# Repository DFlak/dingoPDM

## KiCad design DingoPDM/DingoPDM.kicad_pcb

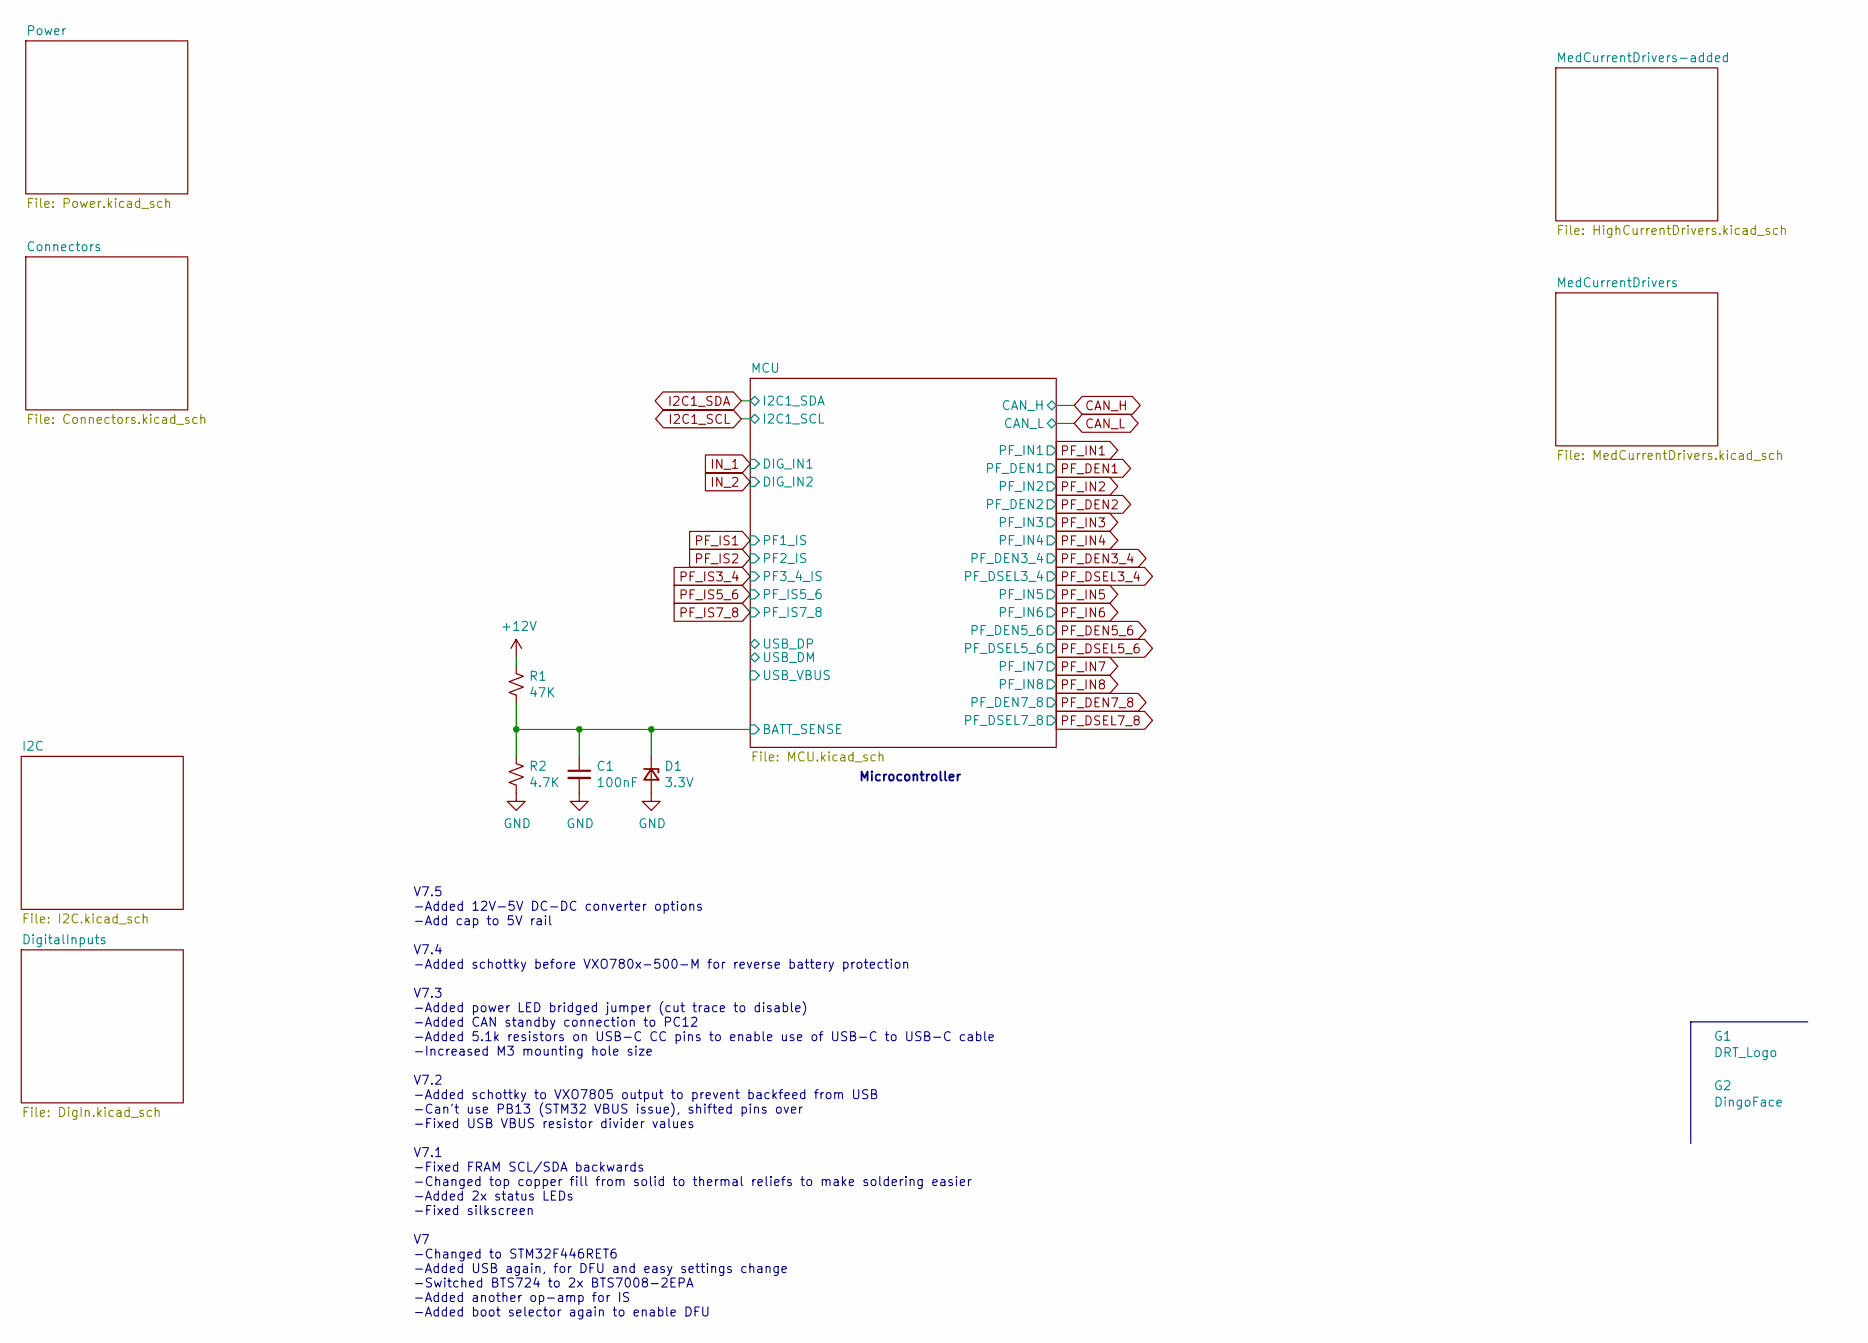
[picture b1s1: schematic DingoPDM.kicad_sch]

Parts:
C1: 100nF; C_0805_2012Metric; Digi-Key_PN 478-1395-1-ND
D1: 3.3V; D_SOD-323_HandSoldering; Digi-Key_PN 1727-5150-1-ND
G1: DRT_Logo; DRTLogo
G2: DingoFace; DingoFaceNoFill
R1: 47K; R_0805_2012Metric; Digi-Key_PN 311-47.0KCRCT-ND
R2: 4.7K; R_0805_2012Metric; Digi-Key_PN 311-4.70KCRCT-ND

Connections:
+12V: R1.1; also elsewhere on the board
/MCU/BATT_SENSE: C1.1, D1.1 (K), R1.2, R2.1; also elsewhere on the board
GND: C1.2, D1.2 (A), R2.2; also elsewhere on the board

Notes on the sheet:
Microcontroller
V7.5 -Added 12V-5V DC-DC converter options -Add cap to 5V rail V7.4 -Added schottky before VXO780x-500-M for reverse battery protection V7.3 -Added power LED bridged jumper (cut trace to disable) -Added CAN standby connection to PC12 -Added 5.1k resistors on USB-C CC pins to enable use of USB-C to 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

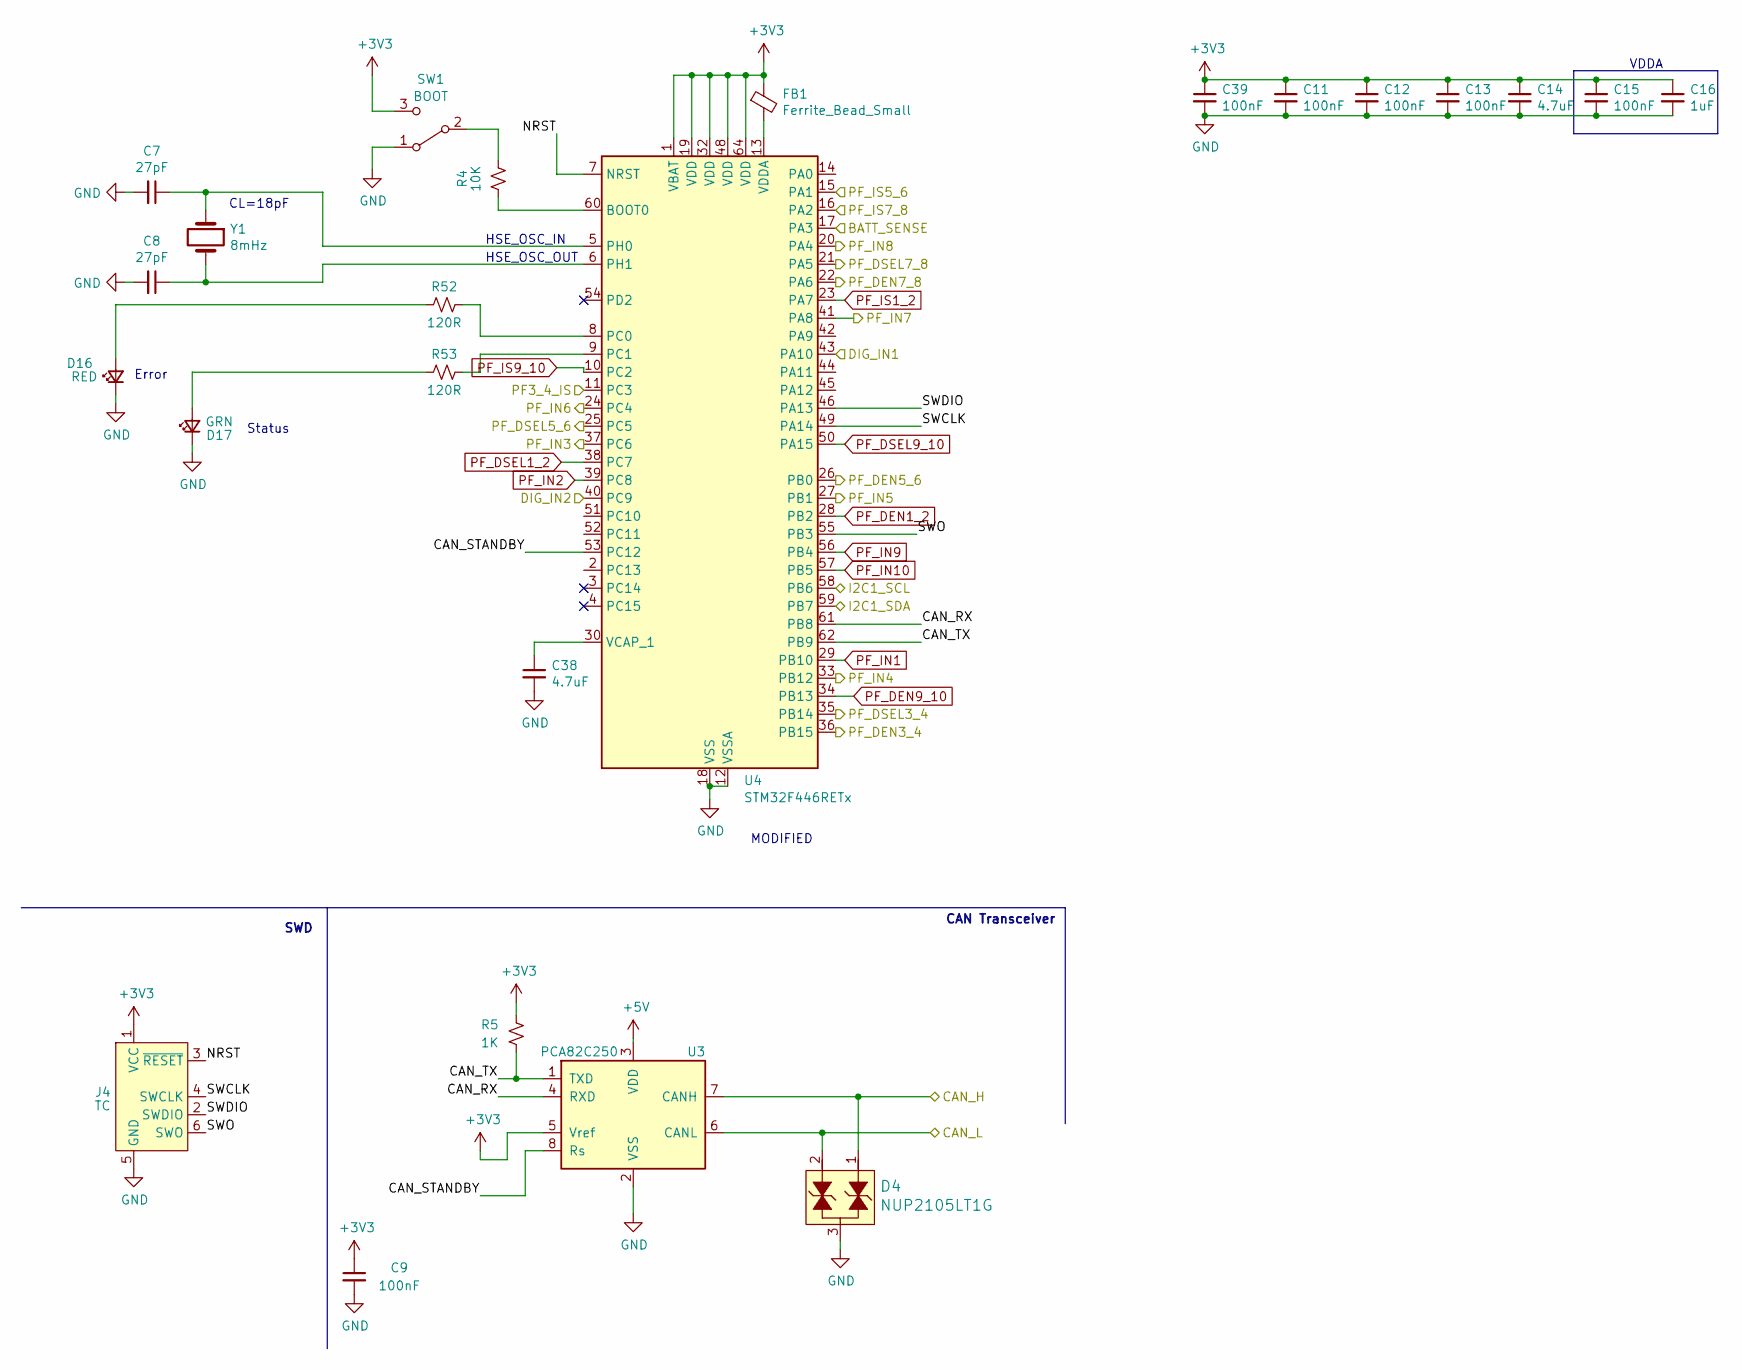
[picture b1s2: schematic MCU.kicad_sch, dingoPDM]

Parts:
C7, C8: 27pF; C_0805_2012Metric; Digi-Key_PN 478-10518-1-ND
C9, C11, C12, C13, C15, C39: 100nF; C_0805_2012Metric; Digi-Key_PN 478-1395-1-ND
C14, C38: 4.7uF; C_0805_2012Metric; Digi-Key_PN 1276-2873-1-ND
C16: 1uF; C_0805_2012Metric; Digi-Key_PN 311-1365-1-ND
D4: NUP2105LT1G; SOT-23-3; Digi-Key_PN NUP2105LT1GOSCT-ND
D16: RED; LED_0805_2012Metric; Digi-Key_PN 475-1278-1-ND
D17: GRN; LED_0805_2012Metric; Digi-Key_PN 475-1410-1-ND
FB1: Ferrite_Bead_Small; R_0805_2012Metric; Digi-Key_PN 490-1054-1-ND
J4: TC; Tag-Connect_TC2030-IDC-NL_2x03_P1.27mm_Vertical
R4: 10K; R_0805_2012Metric; Digi-Key_PN 311-10.0KCRDKR-ND
R5: 1K; R_0805_2012Metric; Digi-Key_PN 311-1.0KARCT-ND
R52, R53: 120R; R_0805_2012Metric; Digi-Key_PN 311-120CRCT-ND
SW1: BOOT; CJS-1200TB; Digi-Key_PN 563-CJS-1200TB1CT-ND
U3: PCA82C250; SOIC-8_3.9x4.9mm_P1.27mm; Digi-Key_PN 568-10316-1-ND
U4: STM32F446RETx; LQFP-64_10x10mm_P0.5mm; Digi-Key_PN 497-15376-ND
Y1: 8mHz; Crystal_SMD_5032-2Pin_5.0x3.2mm_HandSoldering; Digi-Key_PN 535-10630-1-ND

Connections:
+3V3: C9.1, C11.1, C12.1, C13.1, C14.1, C15.1, C16.1, C39.1, FB1.1, J4.1 (VCC), R5.2, SW1.3 (C), U3.5 (Vref), U4.1 (VBAT), U4.19 (VDD), U4.32 (VDD), U4.48 (VDD), U4.64 (VDD); also elsewhere on the board
+5V: U3.3 (VDD); also elsewhere on the board
/MCU/BATT_SENSE: U4.17 (PA3); also elsewhere on the board
/MCU/CAN_RX: U3.4 (RXD), U4.61 (PB8)
/MCU/CAN_STANDBY: U3.8 (Rs), U4.53 (PC12)
/MCU/CAN_TX: R5.1, U3.1 (TXD), U4.62 (PB9)
/MCU/NRST: J4.3 (~RESET), U4.7 (NRST)
/MCU/SWCLK: J4.4 (SWCLK), U4.49 (PA14)
/MCU/SWDIO: J4.2 (SWDIO), U4.46 (PA13)
/MCU/SWO: J4.6 (SWO), U4.55 (PB3)
CAN_H: D4.1, U3.7 (CANH); also elsewhere on the board
CAN_L: D4.2, U3.6 (CANL); also elsewhere on the board
GND: C7.2, C8.2, C9.2, C11.2, C12.2, C13.2, C14.2, C15.2, C16.2, C38.2, C39.2, D4.3, D16.1 (K), D17.1 (K), J4.5 (GND), SW1.1 (A), U3.2 (VSS), U4.12 (VSSA), U4.18 (VSS), U4.31 (VSS), U4.47 (VSS), U4.63 (VSS); also elsewhere on the board
I2C1_SCL: U4.58 (PB6); also elsewhere on the board
I2C1_SDA: U4.59 (PB7); also elsewhere on the board
IN_1: U4.43 (PA10); also elsewhere on the board
IN_2: U4.40 (PC9); also elsewhere on the board
unnamed: D16.2 (A), R52.2
unnamed: D17.2 (A), R53.2
unnamed: R4.1, SW1.2 (B)
unnamed: R4.2, U4.60 (BOOT0)
unnamed: R52.1, U4.8 (PC0)
unnamed: R53.1, U4.9 (PC1)
unnamed: C7.1, U4.5 (PH0), Y1.1
unnamed: C8.1, U4.6 (PH1), Y1.2
unnamed: C38.1, U4.30 (VCAP_1)
unnamed: FB1.2, U4.13 (VDDA)
PF_DEN1_2: U4.28 (PB2); also elsewhere on the board
PF_DEN3_4: U4.36 (PB15); also elsewhere on the board
PF_DEN5_6: U4.26 (PB0); also elsewhere on the board
PF_DEN7_8: U4.22 (PA6); also elsewhere on the board
PF_DEN9_10: U4.34 (PB13); also elsewhere on the board
PF_DSEL1_2: U4.38 (PC7); also elsewhere on the board
PF_DSEL3_4: U4.35 (PB14); also elsewhere on the board
PF_DSEL5_6: U4.25 (PC5); also elsewhere on the board
PF_DSEL7_8: U4.21 (PA5); also elsewhere on the board
PF_DSEL9_10: U4.50 (PA15); also elsewhere on the board
PF_IN1: U4.29 (PB10); also elsewhere on the board
PF_IN2: U4.39 (PC8); also elsewhere on the board
PF_IN3: U4.37 (PC6); also elsewhere on the board
PF_IN4: U4.33 (PB12); also elsewhere on the board
PF_IN5: U4.27 (PB1); also elsewhere on the board
PF_IN6: U4.24 (PC4); also elsewhere on the board
PF_IN7: U4.41 (PA8); also elsewhere on the board
PF_IN8: U4.20 (PA4); also elsewhere on the board
PF_IN9: U4.56 (PB4); also elsewhere on the board
PF_IN10: U4.57 (PB5); also elsewhere on the board
PF_IS1_2: U4.23 (PA7); also elsewhere on the board
PF_IS3_4: U4.11 (PC3); also elsewhere on the board
PF_IS5_6: U4.15 (PA1); also elsewhere on the board
PF_IS7_8: U4.16 (PA2); also elsewhere on the board
PF_IS9_10: U4.10 (PC2); also elsewhere on the board

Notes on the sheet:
SWD
Error
CAN Transceiver
HSE_OSC_IN
MODIFIED
CL=18pF
HSE_OSC_OUT
VDDA
Status

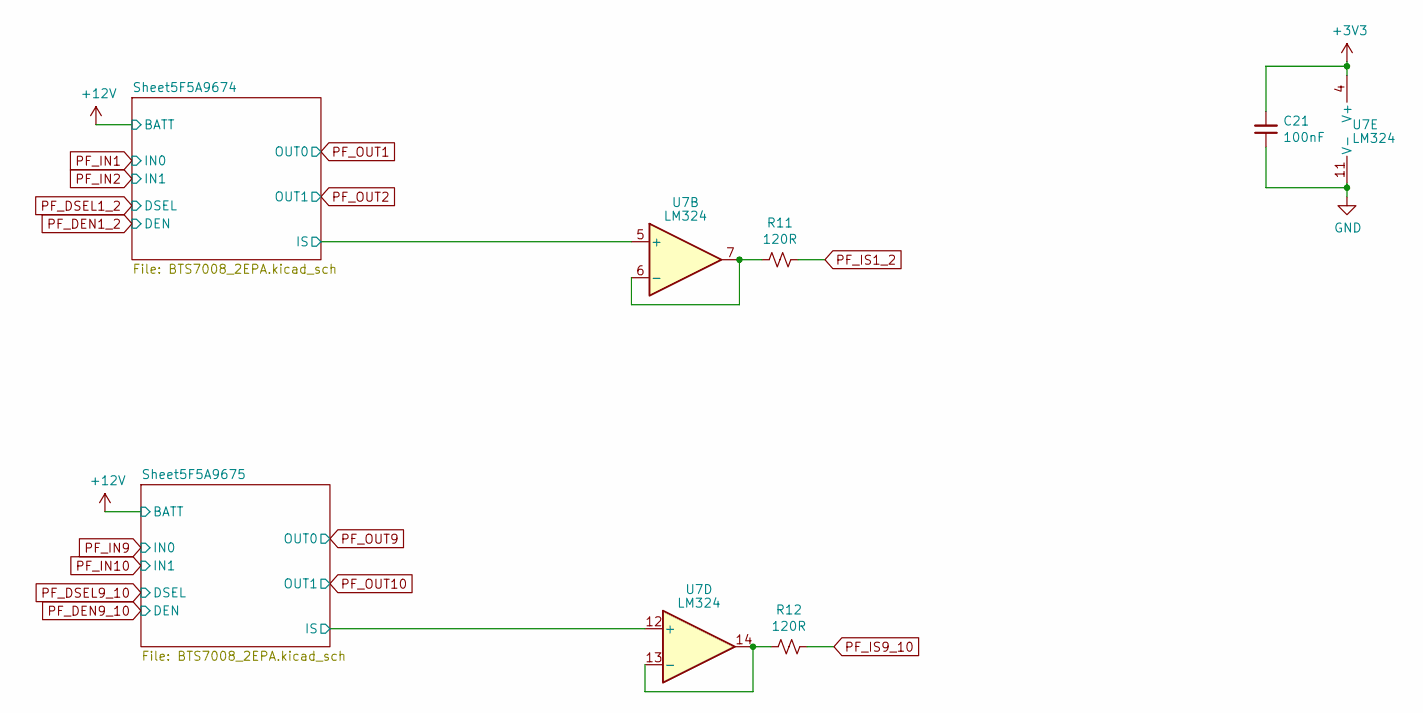
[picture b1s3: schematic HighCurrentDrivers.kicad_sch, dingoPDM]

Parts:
C21: 100nF; C_0805_2012Metric; Digi-Key_PN 478-1395-1-ND
R11, R12: 120R; R_0805_2012Metric; Digi-Key_PN 311-120CRCT-ND
U7: LM324; TSSOP-14_4.4x5mm_P0.65mm; Digi-Key_PN 497-7330-1-ND

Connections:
+3V3: C21.2, U7.4 (V+); also elsewhere on the board
/MedCurrentDrivers-added/Sheet5F5A9674/IS: U7.5 (+); also elsewhere on the board
/MedCurrentDrivers-added/Sheet5F5A9675/IS: U7.12 (+); also elsewhere on the board
/MedCurrentDrivers/Sheet5F5A9674/IS: U7.10 (+); also elsewhere on the board
GND: C21.1, U7.11 (V-); also elsewhere on the board
unnamed: R11.2, U7.6 (-), U7.7
unnamed 47: U7.8, U7.9 (-); also elsewhere on the board
unnamed: R12.2, U7.13 (-), U7.14
PF_IS1_2: R11.1; also elsewhere on the board
PF_IS9_10: R12.1; also elsewhere on the board

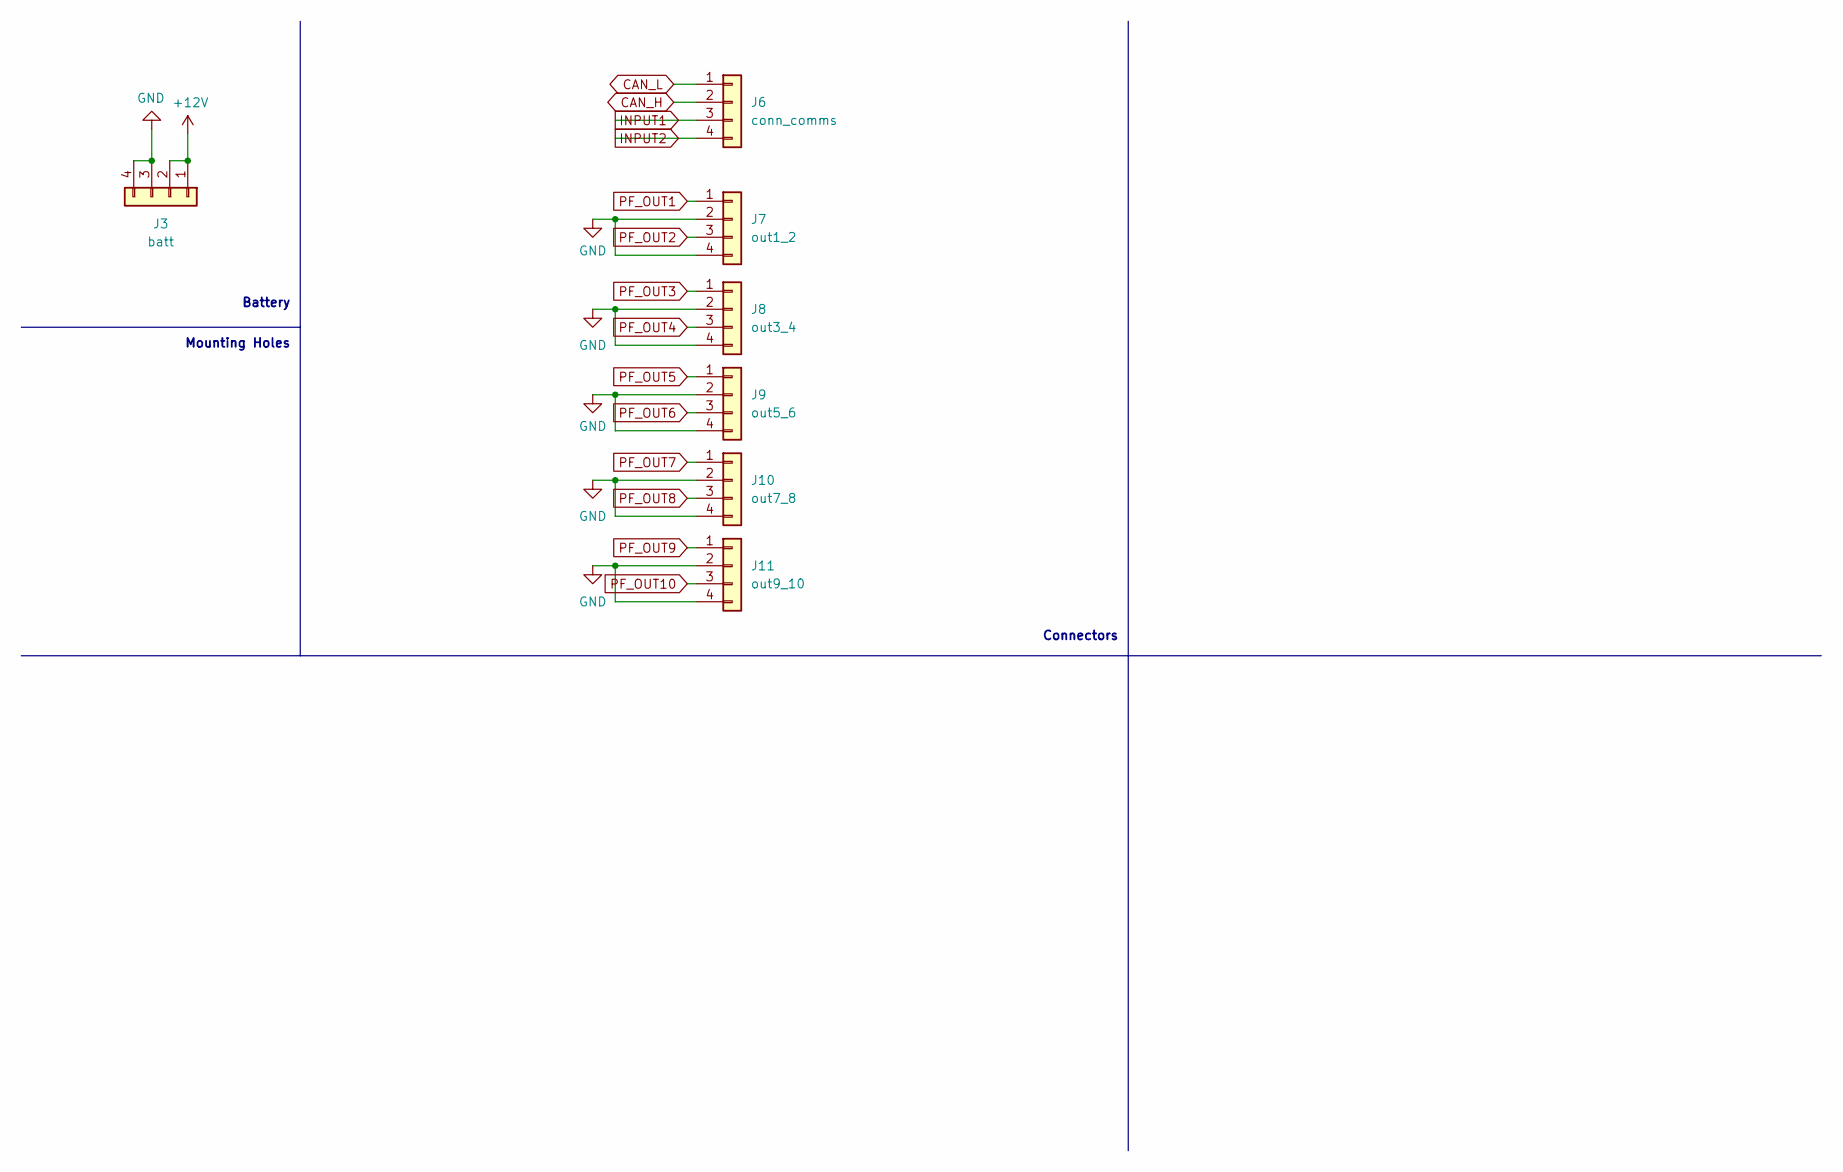
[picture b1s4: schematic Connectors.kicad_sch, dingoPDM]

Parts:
J3: batt; DIP-8_300_ELL
J6: conn_comms; DIP-8_300_ELL
J7: out1_2; DIP-8_300_ELL
J8: out3_4; DIP-8_300_ELL
J9: out5_6; DIP-8_300_ELL
J10: out7_8; DIP-8_300_ELL
J11: out9_10; DIP-8_300_ELL

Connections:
+12V: J3.1, J3.2; also elsewhere on the board
CAN_H: J6.2; also elsewhere on the board
CAN_L: J6.1; also elsewhere on the board
GND: J3.3, J3.4, J7.2, J7.4, J8.2, J8.4, J9.2, J9.4, J10.2, J10.4, J11.2, J11.4; also elsewhere on the board
INPUT1: J6.3; also elsewhere on the board
INPUT2: J6.4; also elsewhere on the board
PF_OUT1: J7.1; also elsewhere on the board
PF_OUT2: J7.3; also elsewhere on the board
PF_OUT3: J8.1; also elsewhere on the board
PF_OUT4: J8.3; also elsewhere on the board
PF_OUT5: J9.1; also elsewhere on the board
PF_OUT6: J9.3; also elsewhere on the board
PF_OUT7: J10.1; also elsewhere on the board
PF_OUT8: J10.3; also elsewhere on the board
PF_OUT9: J11.1; also elsewhere on the board
PF_OUT10: J11.3; also elsewhere on the board

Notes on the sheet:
Connectors
Battery
Mounting Holes

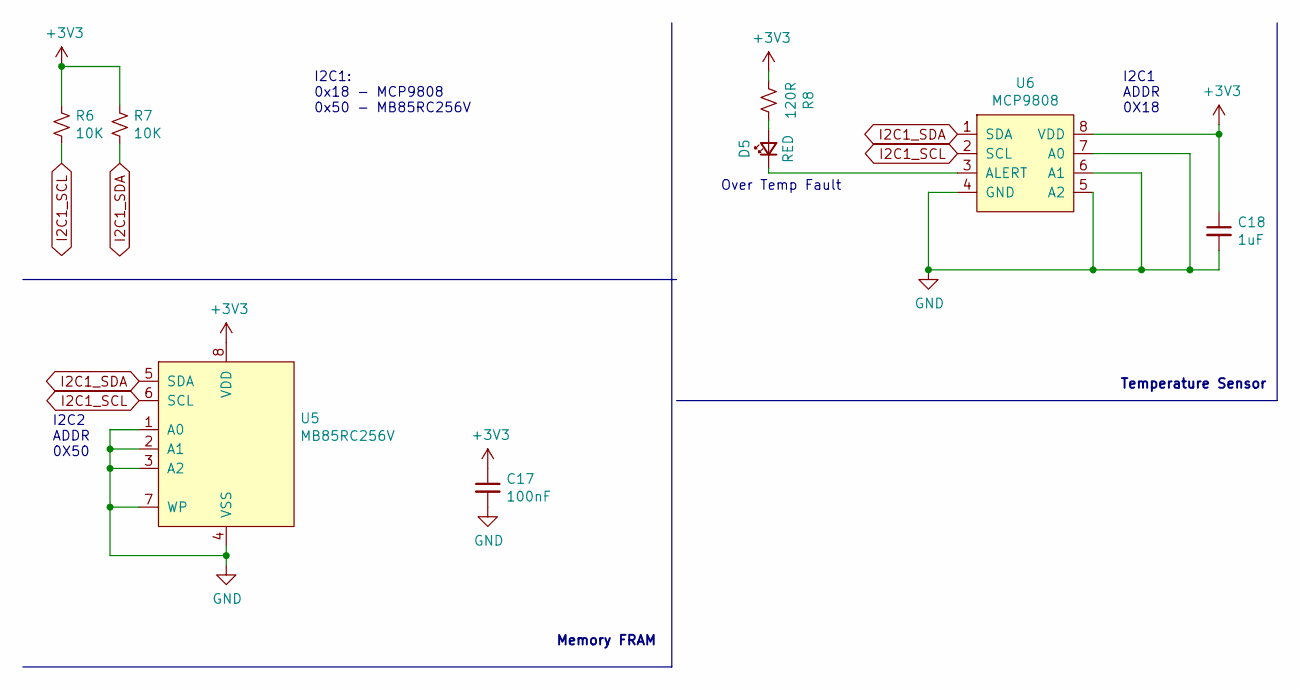
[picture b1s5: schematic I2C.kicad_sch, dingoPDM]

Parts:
C17: 100nF; C_0805_2012Metric; Digi-Key_PN 478-1395-1-ND
C18: 1uF; C_0805_2012Metric; Digi-Key_PN 311-1365-1-ND
D5: RED; LED_0805_2012Metric; Digi-Key_PN 475-1278-1-ND
R6, R7: 10K; R_0805_2012Metric; Digi-Key_PN 311-10.0KCRDKR-ND
R8: 120R; R_0805_2012Metric; Digi-Key_PN 311-120CRCT-ND
U5: MB85RC256V; SOIC-8_3.9x4.9mm_P1.27mm; Digi-Key_PN 865-1261-1-ND
U6: MCP9808; MSOP-8_3x3mm_P0.65mm; Digi-Key_PN MCP9808T-E/MSCT-ND

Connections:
+3V3: C17.1, C18.1, R6.1, R7.1, R8.2, U5.8 (VDD), U6.8 (VDD); also elsewhere on the board
GND: C17.2, C18.2, U5.1 (A0), U5.2 (A1), U5.3 (A2), U5.4 (VSS), U5.7 (WP), U6.4 (GND), U6.5 (A2), U6.6 (A1), U6.7 (A0); also elsewhere on the board
I2C1_SCL: R6.2, U5.6 (SCL), U6.2 (SCL); also elsewhere on the board
I2C1_SDA: R7.2, U5.5 (SDA), U6.1 (SDA); also elsewhere on the board
unnamed: D5.2 (A), R8.1
unnamed: D5.1 (K), U6.3 (ALERT)

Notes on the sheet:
I2C1 ADDR 0X18
I2C2 ADDR 0X50
Over Temp Fault
Temperature Sensor
I2C1: 0x18 - MCP9808 0x50 - MB85RC256V
Memory FRAM

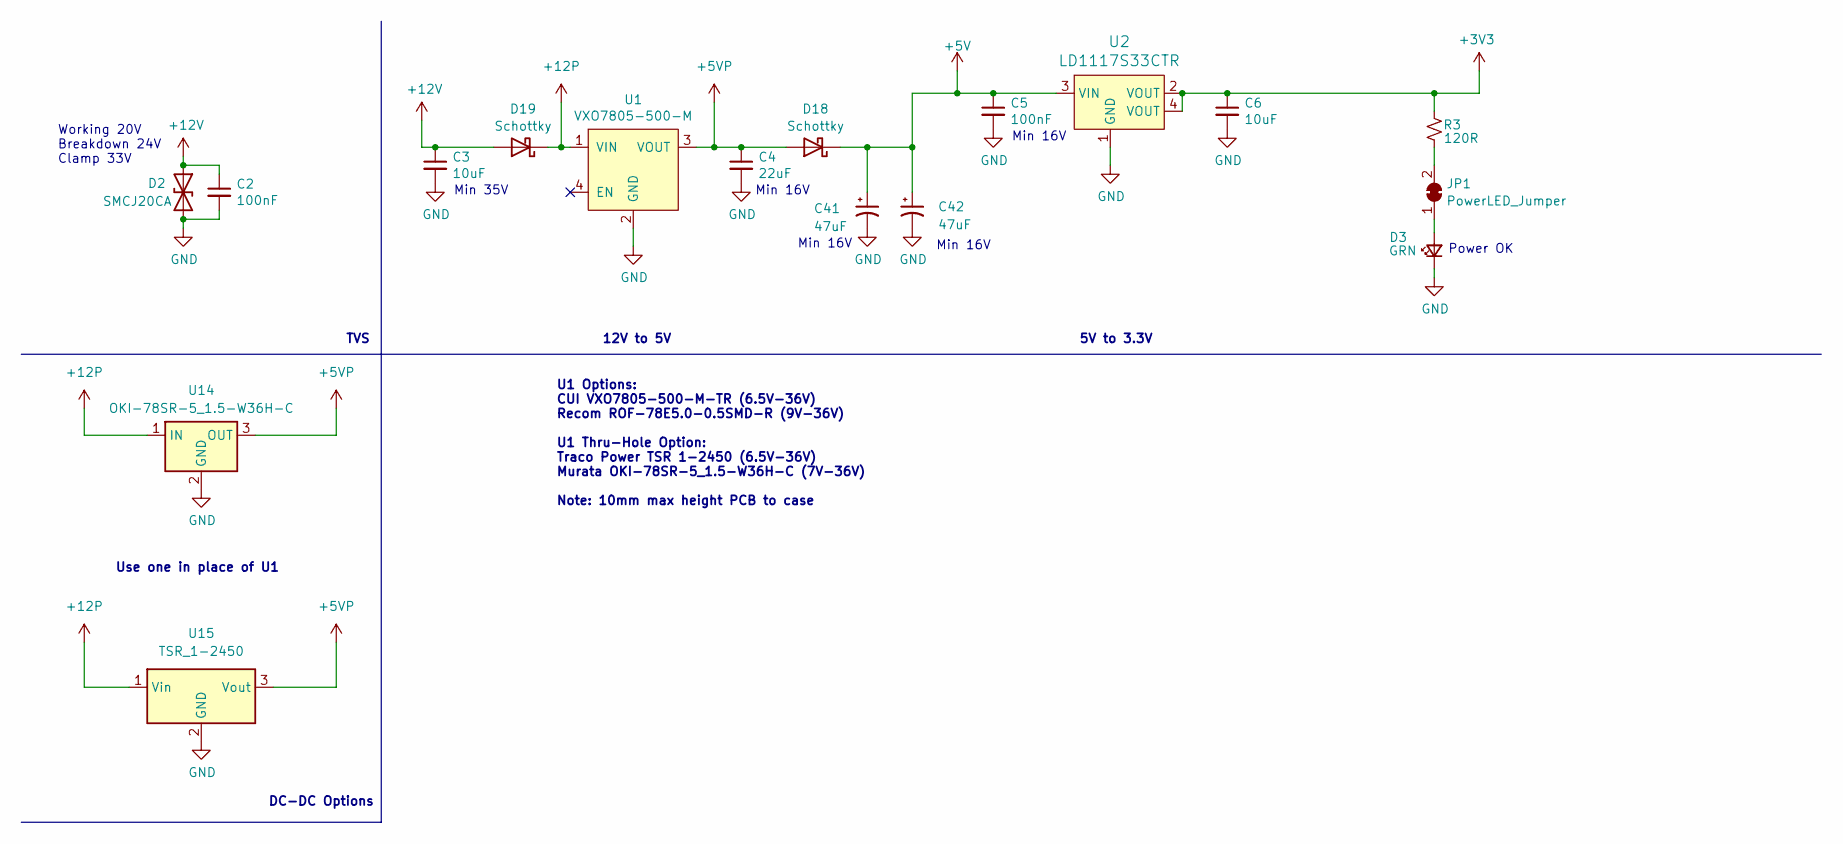
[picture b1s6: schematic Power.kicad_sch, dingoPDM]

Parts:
C2, C5: 100nF; C_0805_2012Metric; Digi-Key_PN 478-1395-1-ND
C3, C6: 10uF; C_0805_2012Metric; Digi-Key_PN 445-11516-1-ND
C4: 22uF; C_0805_2012Metric; Digi-Key_PN 490-10749-1-ND
C41, C42: 47uF; C_2220_5750Metric; Digi-Key_PN 445-7935-1-ND
D2: SMCJ20CA; DO-214AB_TVS; Digi-Key_PN SMCJ20CABCT-ND
D3: GRN; LED_0805_2012Metric; Digi-Key_PN 475-1410-1-ND
D18, D19: Schottky; D_SOD-123; Digi-Key_PN 1727-2394-1-ND
JP1: PowerLED_Jumper; SolderJumper-2_P1.3mm_Bridged_RoundedPad1.0x1.5mm
R3: 120R; R_0805_2012Metric; Digi-Key_PN 311-120CRCT-ND
U1: VXO7805-500-M; VXO78x-500-M; Digi-Key_PN 102-VXO7805-500-M-CT-ND
U2: LD1117S33CTR; SOT-223; Digi-Key_PN 497-1241-1-ND
U14: OKI-78SR-5_1.5-W36H-C; Converter_DCDC_Murata_OKI-78SR_Horizontal
U15: TSR_1-2450; Converter_DCDC_TRACO_TSR-1_THT

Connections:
+3V3: C6.1, R3.2, U2.2 (VOUT), U2.4 (VOUT); also elsewhere on the board
+5V: C5.1, C41.1, C42.1, D18.1 (K), U2.3 (VIN); also elsewhere on the board
+5VP: C4.1, D18.2 (A), U1.3 (VOUT), U14.3 (OUT), U15.3 (Vout)
+12P: D19.1 (K), U1.1 (VIN), U14.1 (IN), U15.1 (Vin)
+12V: C2.1, C3.1, D2.1 (A1), D19.2 (A); also elsewhere on the board
GND: C2.2, C3.2, C4.2, C5.2, C6.2, C41.2, C42.2, D2.2 (A2), D3.1 (K), U1.2 (GND), U2.1 (GND), U14.2 (GND), U15.2 (GND); also elsewhere on the board
unnamed: D3.2 (A), JP1.1 (A)
unnamed: JP1.2 (B), R3.1

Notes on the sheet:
Min 16V
TVS
Min 35V
Power OK
5V to 3.3V
U1 Options: CUI VXO7805-500-M-TR (6.5V-36V) Recom ROF-78E5.0-0.5SMD-R (9V-36V) U1 Thru-Hole Option: Traco Power TSR 1-2450 (6.5V-36V) Murata OKI-78SR-5_1.5-W36H-C (7V-36V) Note: 10mm max height PCB to case
12V to 5V
DC-DC Options
Use one in place of U1
Working 20V Breakdown 24V Clamp 33V

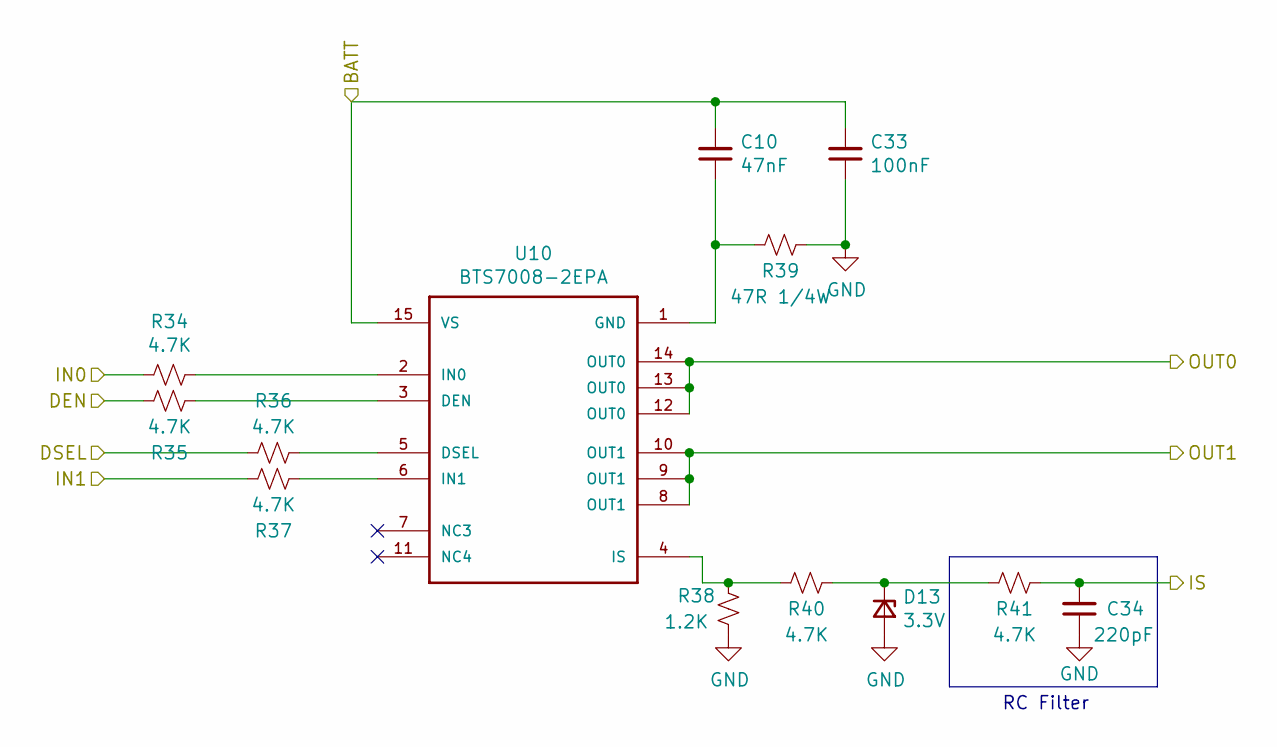
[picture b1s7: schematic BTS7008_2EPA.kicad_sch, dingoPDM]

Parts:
C10: 47nF; C_0805_2012Metric; Digi-Key_PN 399-1166-1-ND
C33: 100nF; C_0805_2012Metric; Digi-Key_PN 478-1395-1-ND
C34: 220pF; C_0805_2012Metric; Digi-Key_PN 399-1138-1-ND
D13: 3.3V; D_SOD-323_HandSoldering; Digi-Key_PN 1727-5150-1-ND
R34, R35, R36, R37, R40, R41: 4.7K; R_0805_2012Metric; Digi-Key_PN 311-4.70KCRCT-ND
R38: 1.2K; R_0805_2012Metric; Digi-Key_PN 311-1.20KCRCT-ND
R39: 47R 1/4W; R_1206_3216Metric; Digi-Key_PN 311-47.0FRCT-ND
U10: BTS7008-2EPA; TDSO-14; Digi-Key_PN BTS70082EPAXUMA1CT-ND

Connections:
+12V: C10.2, C33.2, U10.15 (VS); also elsewhere on the board
/MedCurrentDrivers/Sheet5F5A9675/IS: C34.2, R41.1; also elsewhere on the board
GND: C33.1, C34.1, D13.2 (A), R38.2, R39.1; also elsewhere on the board
unnamed: D13.1 (K), R40.1, R41.2
unnamed: R35.1, U10.3 (DEN)
unnamed: R36.2, U10.5 (DSEL)
unnamed: C10.1, R39.2, U10.1 (GND)
unnamed: R34.1, U10.2 (IN0)
unnamed: R37.1, U10.6 (IN1)
unnamed: R38.1, R40.2, U10.4 (IS)
PF_DEN5_6: R35.2; also elsewhere on the board
PF_DSEL5_6: R36.1; also elsewhere on the board
PF_IN5: R34.2; also elsewhere on the board
PF_IN6: R37.2; also elsewhere on the board
PF_OUT5: U10.12 (OUT0), U10.13 (OUT0), U10.14 (OUT0); also elsewhere on the board
PF_OUT6: U10.8 (OUT1), U10.9 (OUT1), U10.10 (OUT1); also elsewhere on the board

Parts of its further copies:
C22, C25, C30, C35: 47nF; C_0805_2012Metric; Digi-Key_PN 399-1166-1-ND
C23, C26, C31, C36: 100nF; C_0805_2012Metric; Digi-Key_PN 478-1395-1-ND
C24, C27, C32, C37: 220pF; C_0805_2012Metric; Digi-Key_PN 399-1138-1-ND
D8, D9, D12, D14: 3.3V; D_SOD-323_HandSoldering; Digi-Key_PN 1727-5150-1-ND
R13, R14, R15, R16, R17, R20, R21, R22, R23, R24, R26, R27, R28, R29, R32, R33, R43, R44, R45, R46, R49, R50, R60, R61: 4.7K; R_0805_2012Metric; Digi-Key_PN 311-4.70KCRCT-ND
R18, R30, R47, R58: 1.2K; R_0805_2012Metric; Digi-Key_PN 311-1.20KCRCT-ND
R19, R31, R48, R59: 47R 1/4W; R_1206_3216Metric; Digi-Key_PN 311-47.0FRCT-ND
U8, U9, U11, U13: BTS7008-2EPA; TDSO-14; Digi-Key_PN BTS70082EPAXUMA1CT-ND

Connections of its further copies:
+12V: C22.2, C23.2, C25.2, C26.2, C30.2, C31.2, C35.2, C36.2, U8.15 (VS), U9.15 (VS), U11.15 (VS), U13.15 (VS); also elsewhere on the board
/MedCurrentDrivers-added/Sheet5F5A9674/IS: C24.2, R21.1; also elsewhere on the board
/MedCurrentDrivers-added/Sheet5F5A9675/IS: C27.2, R61.1; also elsewhere on the board
/MedCurrentDrivers/Sheet5F5A9674/IS: C32.2, R33.1; also elsewhere on the board
/MedCurrentDrivers/Sheet5F5A9676/IS: C37.2, R50.1; also elsewhere on the board
GND: C23.1, C24.1, C26.1, C27.1, C31.1, C32.1, C36.1, C37.1, D8.2 (A), D9.2 (A), D12.2 (A), D14.2 (A), R18.2, R19.1, R30.2, R31.1, R47.2, R48.1, R58.2, R59.1; also elsewhere on the board
unnamed: D8.1 (K), R20.1, R21.2
unnamed: D9.1 (K), R60.1, R61.2
unnamed: D12.1 (K), R32.1, R33.2
unnamed: D14.1 (K), R49.1, R50.2
unnamed: R22.1, U8.3 (DEN)
unnamed: R23.2, U8.5 (DSEL)
unnamed: C25.1, R59.2, U8.1 (GND)
unnamed: R13.1, U8.2 (IN0)
unnamed: R24.1, U8.6 (IN1)
unnamed: R58.1, R60.2, U8.4 (IS)
unnamed: R15.1, U9.3 (DEN)
unnamed: R16.2, U9.5 (DSEL)
unnamed: C22.1, R19.2, U9.1 (GND)
unnamed: R14.1, U9.2 (IN0)
unnamed: R17.1, U9.6 (IN1)
unnamed: R18.1, R20.2, U9.4 (IS)
unnamed: R27.1, U11.3 (DEN)
unnamed: R28.2, U11.5 (DSEL)
unnamed: C30.1, R31.2, U11.1 (GND)
unnamed: R26.1, U11.2 (IN0)
unnamed: R29.1, U11.6 (IN1)
unnamed: R30.1, R32.2, U11.4 (IS)
unnamed: R44.1, U13.3 (DEN)
unnamed: R45.2, U13.5 (DSEL)
unnamed: C35.1, R48.2, U13.1 (GND)
unnamed: R43.1, U13.2 (IN0)
unnamed: R46.1, U13.6 (IN1)
unnamed: R47.1, R49.2, U13.4 (IS)
PF_DEN1_2: R15.2; also elsewhere on the board
PF_DEN3_4: R27.2; also elsewhere on the board
PF_DEN7_8: R44.2; also elsewhere on the board
PF_DEN9_10: R22.2; also elsewhere on the board
PF_DSEL1_2: R16.1; also elsewhere on the board
PF_DSEL3_4: R28.1; also elsewhere on the board
PF_DSEL7_8: R45.1; also elsewhere on the board
PF_DSEL9_10: R23.1; also elsewhere on the board
PF_IN1: R14.2; also elsewhere on the board
PF_IN2: R17.2; also elsewhere on the board
PF_IN3: R26.2; also elsewhere on the board
PF_IN4: R29.2; also elsewhere on the board
PF_IN7: R43.2; also elsewhere on the board
PF_IN8: R46.2; also elsewhere on the board
PF_IN9: R13.2; also elsewhere on the board
PF_IN10: R24.2; also elsewhere on the board
PF_OUT1: U9.12 (OUT0), U9.13 (OUT0), U9.14 (OUT0); also elsewhere on the board
PF_OUT2: U9.8 (OUT1), U9.9 (OUT1), U9.10 (OUT1); also elsewhere on the board
PF_OUT3: U11.12 (OUT0), U11.13 (OUT0), U11.14 (OUT0); also elsewhere on the board
PF_OUT4: U11.8 (OUT1), U11.9 (OUT1), U11.10 (OUT1); also elsewhere on the board
PF_OUT7: U13.12 (OUT0), U13.13 (OUT0), U13.14 (OUT0); also elsewhere on the board
PF_OUT8: U13.8 (OUT1), U13.9 (OUT1), U13.10 (OUT1); also elsewhere on the board
PF_OUT9: U8.12 (OUT0), U8.13 (OUT0), U8.14 (OUT0); also elsewhere on the board
PF_OUT10: U8.8 (OUT1), U8.9 (OUT1), U8.10 (OUT1); also elsewhere on the board

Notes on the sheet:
RC Filter

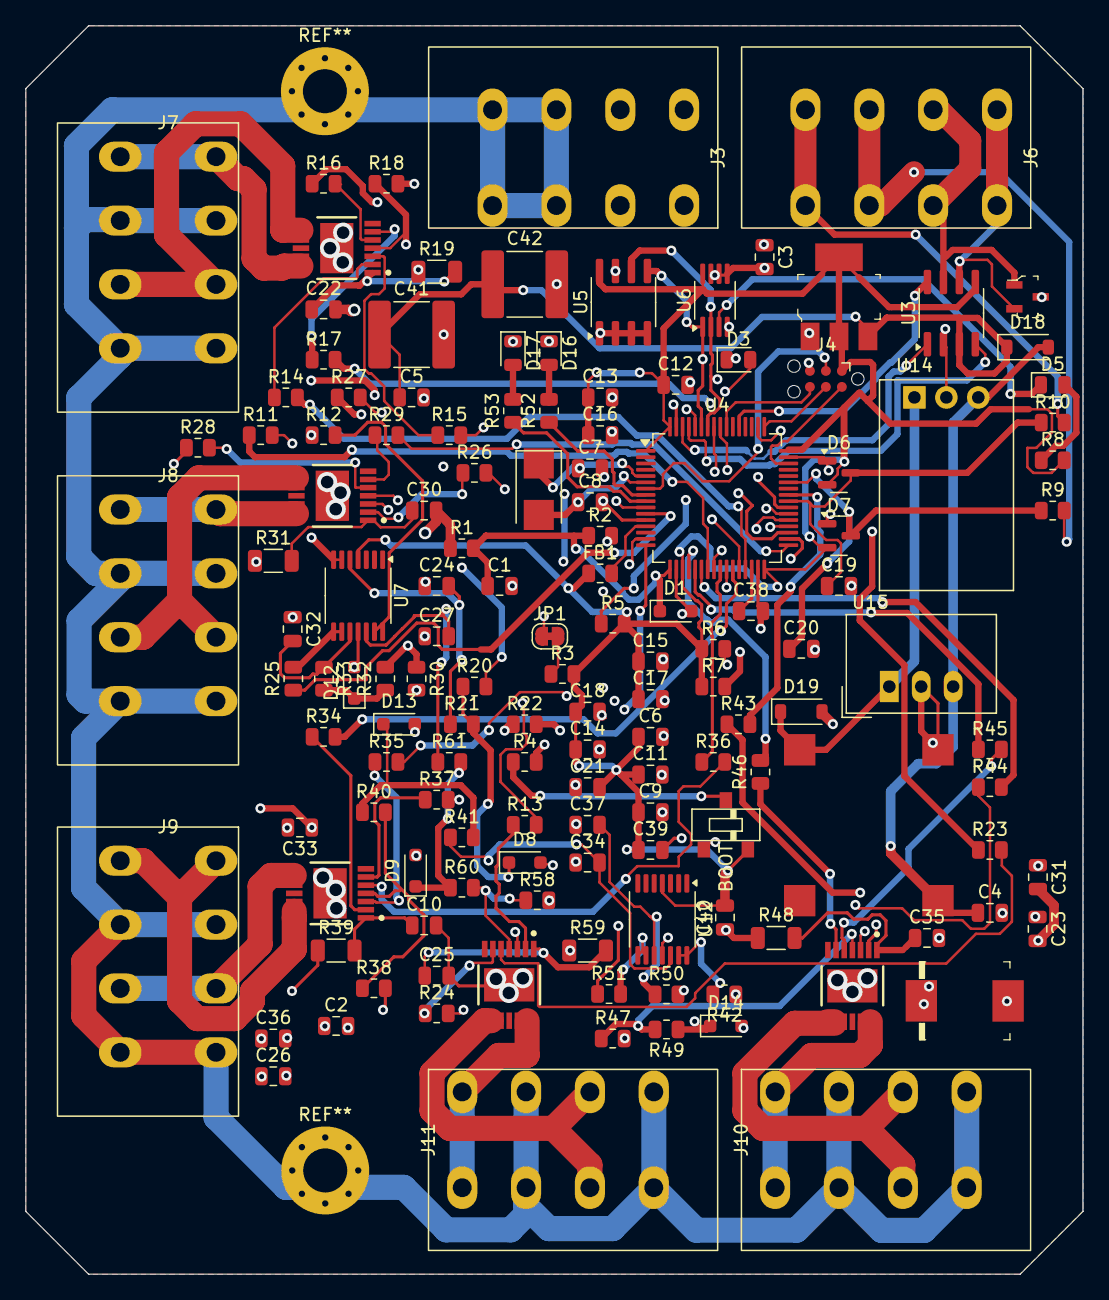
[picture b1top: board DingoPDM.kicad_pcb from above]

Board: 4 copper layers, 84.1 x 99.3 mm, 140 parts (0 on the bottom side), 116 nets.

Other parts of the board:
C19, C20: 10nF; C_0805_2012Metric
C40: 100nF; C_0805_2012Metric
D6, D7: BAT54S; SOT-23
R9, R10: 4.7K; R_0805_2012Metric
R25, R42, R51: 120R; R_0805_2012Metric
U12: LM324; TSSOP-14_4.4x5mm_P0.65mm

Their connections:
+3V3: C40.2, D6.2, D7.2, U12.4 (V+); also elsewhere on the board
/MedCurrentDrivers/Sheet5F5A9675/IS: U12.12 (+); also elsewhere on the board
/MedCurrentDrivers/Sheet5F5A9676/IS: U12.10 (+); also elsewhere on the board
GND: C19.2, C20.2, C40.1, D6.1, D7.1, U12.11 (V-); also elsewhere on the board
INPUT1: R9.2; also elsewhere on the board
INPUT2: R10.2; also elsewhere on the board
IN_1: C20.1, D7.3, R9.1; also elsewhere on the board
IN_2: C19.1, D6.3, R10.1; also elsewhere on the board
unnamed 47: R25.2; also elsewhere on the board
unnamed: R51.2, U12.8, U12.9 (-)
unnamed: R42.2, U12.13 (-), U12.14
PF_IS3_4: R25.1; also elsewhere on the board
PF_IS5_6: R42.1; also elsewhere on the board
PF_IS7_8: R51.1; also elsewhere on the board

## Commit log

2025-12-28 Modified PCB for 10ch PDM board
    I modified the original dingoPDM for 10 channels. The board has been manufactured, tested and works but after mounting I decided that it doesn't suit my needs for the current build. I may develop it 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
